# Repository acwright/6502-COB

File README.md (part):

6502-COB
========

An **AC6502** retro-style 8-bit computer based on the **65C02** microprocessor.

> 📖 **Guide:** [AC6502 Documentation](https://acwright.github.io/6502-DOCS/) — the user's and programmer's guide for the whole family.
> See [COB's page in the family appendix](https://acwright.github.io/6502-DOCS/family/cob).

---

**Building one? Every part you need, with supplier numbers and known issues, is in [BOM.md](BOM.md).**

## Table of Contents

- [Overview](#overview)
- [Architecture](#architecture)
- [Systems](#systems)
- [Software](#software)
- [Hardware](#hardware)
  - [Backplanes](#backplanes)
  - [Cards](#cards)
  - [Helpers](#helpers)
- [Which revision to make](#which-revision-to-make)
- [Firmware](#firmware)
  - [KEH Controller](#keh-controller)
  - [PS2 Keyboard Controller](#ps2-keyboard-controller)
  - [STP Controller](#stp-controller)
- [CAD](#cad)
- [Production](#production)
- [Schematics](#schematics)
- [Shared lines](#shared-lines)
- [Extra pins: `EXP0`–`EXP3` and `HRDB`](#extra-pins-exp0exp3-and-hrdb)
- [Jumpers](#jumpers)
- [Off-board headers](#off-board-headers)
- [Checking the schematics](#checking-the-schematics)
- [Libraries](#libraries)
- [Bill of Materials](#bill-of-materials)
- [Purchase](#purchase)
- [License](#license)

---

## Overview

The AC6502 ecosystem is a family of open-source, 65C02-based computers sharing a common architecture, memory map, and [BIOS](https://github.com/acwright/6502-BIOS). Each computer in the family is purpose-built for a different use case but runs the same software and firmware.

The **COB** (Computer on a Backplane) is a full-featured modular desktop computer. It features a real 65C02 CPU, a backplane architecture with expandable card slots, up to 544KB RAM, composite or VGA video output, CompactFlash or SD storage, a real-time clock, and support for PS/2 keyboards, matrix keyboards, and Atari 2600-compatible joysticks.

## Architecture

All AC6502 computers share:

- **CPU**: 65C02 (or accurate emulation)
- **Memory**: 32KB RAM + 32KB ROM, with optional banked RAM expansion
- **Memory Map**: Standardized across the ecosystem — zero page, stack, I/O space ($8000–$9FFF), system ROM, and interrupt vectors at $FFFA–$FFFF
- **Bus**: 16-bit address bus, 8-bit bidirectional data bus, standard 65C02 control signals (RW, PHI2, RESET, IRQ, NMI, RDY, SYNC)
- **BIOS**: A common [BIOS](https://github.com/acwright/6502-BIOS) provides the kernel, monitor, and BASIC interpreter across all systems

## Systems

| Project | Description |
|---------|-------------|
| [6502-ACE](https://github.com/acwright/6502-ACE) | All-in-one Computer Experience — A single board computer |
| [6502-COB](https://github.com/acwright/6502-COB) | Computer On a Backplane — Modular desktop computer with expandable card slots (YOU ARE HERE) |
| [6502-DEV](https://github.com/acwright/6502-DEV) | Development Environment Vehicle — Emulation-based dev system |
| [6502-KIM](https://github.com/acwright/6502-KIM) | Keypad Input Monitor - KIM-1 inspired minimal computer |
| [6502-VCS](https://github.com/acwright/6502-VCS) | Video Computer System — Cartridge-based retro gaming console |

## Software

| Project | Description |
|---------|-------------|
| [6502-BIOS](https://github.com/acwright/6502-BIOS) | The shared BIOS (kernel, monitor, BASIC) for all AC6502 computers |
| [6502-EMULATOR](https://github.com/acwright/6502-EMULATOR) | Emulator for the whole family — desktop app, browser build, and a command line for scripted runs |
| [6502-PRG](https://github.com/acwright/6502-PRG) | Template project for writing assembly language programs |
| [6502-CRT](https://github.com/acwright/6502-CRT) | Template project for writing assembly language cartridges |
| [6502-ASM](https://github.com/acwright/6502-ASM) | Assembly language example programs and demos |
| [6502-BAS](https://github.com/acwright/6502-BAS) | BASIC program listings |
| [6502-WOZMON](https://github.com/acwright/6502-WOZMON) | Wozmon as a standalone ROM |
| [6502-NOP](https://github.com/acwright/6502-NOP) | An all-NOP ROM, for probing a board during bring-up |
| [6502-DOCS](https://github.com/acwright/6502-DOCS) | The documentation site — the guide, the printable reference cards, branding and label artwork |
| [cffs](https://github.com/acwright/cffs) | Builds CompactFlash disk images for the BIOS filesystem |
| [bastok](https://github.com/acwright/bastok) | Tokenizes BASIC listings into `.prg` images, and back |
| [bin2woz](https://github.com/acwright/bin2woz) | Converts a binary into a Wozmon serial upload |

## Hardware

This repository contains KiCad 7.0+ PCB designs for the backplanes, cards, and helpers that make up the COB system.

### Backplanes

**`Hardware/Backplane/`** — Passive backplane providing 5 card slots with full bus interconnect across all slots.

**`Hardware/Backplane Pro/`** — Enhanced backplane with integrated clock generation, reset circuitry, and power distribution plus 5 card slots. Rev 1.1 moves to entirely through-hole components and adds an onboard power switch and DC barrel jack input. Today's Rev 1.1 also removes the `RESB` pull-up and adds reverse-polarity protection on the barrel jack; the boards made as Rev 1.1, which are on sale, have neither change (see the build notes in BOM.md). Every revision's oscillator can is 1 MHz, and serial is tested at 1 MHz. A faster can is at the builder's risk, because the serial cards haven't been tested with one.

**`Hardware/Backplane Helper/`** — Adds additional card slots to expand the total backplane configuration up to 12 slots.

### Cards

**`Hardware/Clock Card/`** — The Backplane Pro's clock, reset and power on a card, so a COB can be built on the passive Backplane: a 1 MHz DIP-14 can oscillator to `PHI2` through a clock-enable header (so the Clock Helper's single-step and halt still work), the 555 power-on and push-button reset pulling `RESB` low through an NPN, and a 5 V barrel jack with reverse-polarity protection. Serial is tested at 1 MHz, so a faster oscillator can is at the builder's risk, as on the Backplane Pro. *(Ordered, not yet built)*

**`Hardware/CPU Card/`** — Hosts the 65C02 CPU in a card form factor for backplane-based COB systems. Its `EXP` header, J3, can jumper `EXP0` to VPB and `EXP1` to MLB. Leave those two positions open in a build that takes cartridges, because a cartridge grounds `EXP0` and `EXP1` (see [Extra pins](#extra-pins-exp0exp3-and-hrdb)).

**`Hardware/CPU Card Pro/`** — Hosts a 65816 16-bit CPU (backward-compatible with 65C02). *(Untested)* Its title block credits bahamutkotd, who contributed. Its `EXP` header, J3, can jumper `EXP0` to VPB and `EXP1` to MLB; as on the CPU Card, leave those positions open in a build that takes cartridges. J2, `BANK ADDR`, carries the 65816's bank byte (address bits A16–A23), which U4 latches while `PHI2` is low and holds through the rest of the cycle. It is how a 65816 on this card reaches past 64 KB, for a breadboard or a card of your own. Nothing in the family uses it yet, and it is unproven until the card is built. The RAM Card Rev 1.0's J4 has the same pinout; see its build notes before joining the two.

**`Hardware/Memory Card/`** — Provides 32KB SRAM and 32KB EEPROM with address decoding logic for COB systems using the CPU Card. J2 (or the solder jumpers JP1 and JP2) joins the bus's `EXP1` and `EXP0` to the ROM's `HRDB`: fit both in a COB that takes cartridges. See [Extra pins](#extra-pins-exp0exp3-and-hrdb).

**`Hardware/RAM Card/`** — 512KB banked RAM expansion organized as two 256KB banks with 256 × 1KB windows each. Rev 1.1 has the ACE Board's circuit, with a bank latch for each window; Rev 1.0 has one latch for both. Rev 1.0's J4, `BANK ADDR`, carries the bank latch's outputs: an untested experiment that nothing in the family uses, which the build notes in [BOM.md](BOM.md#ram-card) explain.

**`Hardware/RTC Card/`** — Real-time clock via Dallas DS1511Y with battery backup and 256 bytes of battery-backed SRAM.

**`Hardware/GPIO Card/`** — General-purpose I/O via 65C22 VIA supporting keyboards, joysticks, timers, and custom devices.

**`Hardware/Serial Card/`** — RS-232 serial communication via R6551AP ACIA and MAX232 level shifter.
Female DB-9 wired as **DCE**, so a straight-through cable reaches a PC. `DCD` and `DSR` are tied to
ground; `DTR` is not connected. The `CTS EN` jumper (J4) picks whether the ACIA's `CTS` comes from
ground or from the cable — **ground is the default**, which leaves the transmitter always free to
send. Serial is tested at 1 MHz, the speed of the oscillator can on the Backplane Pro and the Clock
Card. A faster can is at the builder's risk.

**`Hardware/Serial Card Pro/`** — Enhanced serial card with full modem control signals (DTR, DCD, DSR).
Male DB-9 wired as **DTE**, like a PC, so reaching a laptop needs a **null-modem** cable — unlike the
plain Serial Card. `CTS`, `DSR` and `DTR` always reach the cable; the `DCD EN` jumper picks ground or
the cable for `DCD` — **ground is the default**. Serial is tested at 1 MHz, the speed of the
oscillator can on the Backplane Pro and the Clock Card. A faster can is at the builder's risk.

**The handshake lines are not decoration.** On a real R6551, measured on a KIM in 2026: `CTS` high
stops the transmitter dead, and `DCD` high stops the receiver and the arriving byte is lost. A card
jumpered to take either from the cable, plugged into something that does not assert them, looks like
a dead board — no banner, no echo — until the line comes back. Ground is the default for exactly
that reason.

**`Hardware/VGA Card/`** — VGA 640×480 video output via Raspberry Pi Pico running [Pico9918](https://github.com/visrealm/pico9918) with TMS9918A-compatible graphics modes.

**`Hardware/VGA Card Pro/`** — Fully programmable VGA output using Pi Pico with custom firmware. *(Untested)*

**`Hardware/Video Card/`** — Composite video output via TMS9918A Video Display Processor with 16KB video RAM.

**`Hardware/Video Card Pro/`** — Enhanced composite video card. *(Never made)*

**`Hardware/Sound Card/`** — 3-voice SID audio output via ARMSID module with RCA line-level output.

**`Hardware/Storage Card/`** — CompactFlash storage interface supporting up to 128GB via IDE-compatible protocol.

**`Hardware/Storage Card Pro/`** — SD card (up to 32GB) and 16MB onboard SPI flash storage interface. *(Untested, experimental — the stock BIOS has no driver for it; see [STP Controller](#stp-controller))*

**`Hardware/LCD Card/`** — 16×2 character LCD display via 65C22 VIA in 4-bit or 8-bit mode.

**`Hardware/Blinkenlights Card/`** — Visual bus monitoring with LEDs showing address bus (16), data bus (8), and control signals (8) in real time.

**`Hardware/Prototype Card/`** — Blank prototyping area with integrated breadboard and full bus access headers.

### Helpers

**`Hardware/Keyboard Encoder Helper/`** — ATmega1284-based dual keyboard encoder supporting PS/2 keyboard and 8×8 matrix keyboard simultaneously via 65C22 VIA.

**`Hardware/PS2 Helper/`** — ATmega328p-based PS/2 keyboard bridge that drives an MT8808 analog crosspoint switch to emulate a matrix keyboard. Its output is a raw 8×8 matrix and feeds the matrix inputs of a Keyboard Encoder Helper, which is what talks to the 65C22 VIA — not the VIA directly.

**`Hardware/Keyboard Helper/`** — 64-key matrix keyboard with Atari 2600-compatible joystick support.

**`Hardware/GPIO Helper/`** — 8 buttons and 8 LEDs for testing and debugging GPIO Card connections.

**`Hardware/GPIO Breadboard Helper/`** — Breadboard interface adapter for the GPIO Card.

**`Hardware/Joystick Helper/`** — Atari 2600-style dual joystick connector and interface board.

**`Hardware/Clock Helper/`** — Manual clock control providing single-step, free-run, and halt modes for debugging real CPU systems.

**`Hardware/DB25 Helper/`** — GPIO to DB25 connector adapter for external device interfacing.

**`Hardware/Breadboard Helper/`** — Exposes the full AC6502 bus to a breadboard for prototyping and experimentation.

**`Hardware/Mega Helper/`** — Arduino Mega 2560 interface adapter for the AC6502 bus. Arduino pins D6 and D5 are wired to `EXP1` and `EXP0`: with a cartridge on the bus, firmware must leave them as inputs, because the cartridge grounds them (see [Extra pins](#extra-pins-exp0exp3-and-hrdb)).

**LCD Board** — moved to [6502-DEV](https://github.com/acwright/6502-DEV) as the DEV LCD Board on 2026-11-14: it is a DEV board.

**`Hardware/VERA Helper/`** — VERA FPGA video module adapter for the AC6502 bus.

<!-- Which revision to make: generated by Tools/revision-audit/register.py from Tools/data/orders.json. Edit that file, not this section. -->
## Which revision to make

**Make the newest revision of a board, and check its label first.** The table below gives each board's newest revision. A newer revision fixes what was found on the older ones. Every revision, old and new, is in [REVISIONS.md](REVISIONS.md), with what changed in each.

Each revision carries one of three labels:

- **Tested:** This revision was built and tested.
- **Proven design:** Not built at this revision, but its circuit is a tested revision's. The only changes are silkscreen text, part values, mounting holes, outline clean-up, parts moved a fraction of a millimetre onto their grid, capacitor pitch, socket outlines, a footprint swap with the same holes, a solder jumper's default, the solder mask or paste at a card edge, or tracks rerouted or pours refilled with DRC and the netlist check passing. A builder can treat it as tested.
- **Untested:** The circuit, the power path or the layout changed in a way that only a built board proves, or the board has never been built at all.

[BOM.md](BOM.md) has the parts for every revision, and its known issues.

| Board | Newest revision | Label | Why |
|---|---|---|---|
| Backplane | 1.1 | **Proven design** | JLCPCB's marker removed and the logo moved; silkscreen only. |
| Backplane Helper | 1.1 | **Proven design** | JLCPCB's marker removed and the logo moved; silkscreen only. |
| Backplane Pro | 1.1 | **Untested** | The made Rev 1.1 with a 1N5819 in the power path (`VCC` near 4.6 V) and R5 removed. |
| Blinkenlights Card | 1.1 | **Untested** | Decoupling capacitors added, the RESB, IRQB and NMIB LEDs driven through inverters, every inverter a 74HC3G04, tracks rerouted, and the bare card edge. |
| Breadboard Helper | 1.1 | **Proven design** | J1 takes the box header's footprint, with the same holes, and the outline grows to hold it. |
| CPU Card | 1.1 | **Proven design** | 10k pull-ups, some tracks rerouted, silkscreen, the bare card edge. |
| CPU Card Pro | 1.1 | **Untested** | Never made. |
| Clock Card | 1.1 | **Untested** | The bare card edge only, but Rev 1.0 hasn't been tested yet. |
| Clock Helper | 1.1 | **Proven design** | Mounting holes moved to the standard, silkscreen. |
| DB25 Helper | 1.1 | **Proven design** | Mounting holes moved to the standard, silkscreen. |
| GPIO Breadboard Helper | 1.1 | **Proven design** | Outline clean-up. |
| GPIO Card | 1.1 | **Proven design** | The bare card edge only. |
| GPIO Helper | 1.1 | **Proven design** | Mounting holes moved to the standard, silkscreen. |
| Joystick Helper | 1.1 | **Proven design** | Mounting holes moved to the standard, silkscreen. |
| Keyboard Encoder Helper | 1.1 | **Proven design** | Mounting holes, silkscreen. |
| Keyboard Helper | 1.1 | **Proven design** | JLCPCB's marker removed and the logo moved; silkscreen only. |
| LCD Card | 1.1 | **Proven design** | The bare card edge only. |
| Mega Helper | 1.1 | **Proven design** | JLCPCB's marker removed, J1's reference resized and the logo moved; silkscreen only. |
| Memory Card | 1.1 | **Proven design** | The bare card edge, and a 74HCT00 at U5. |
| PS2 Helper | 1.1 | **Proven design** | Resistors moved and tracks rerouted, mounting holes, silkscreen. |
| Prototype Card | 1.1 | **Proven design** | The bare card edge only. |
| RAM Card | 1.1 | **Untested** | The ACE 1.1's banked-RAM circuit: a bank latch for each window, a diode chip select, a 74HCT00 for `RB` and `WB`, and no `LATCH EN` or `BANK ADDR` header. |
| RTC Card | 1.1 | **Proven design** | The bare card edge, and JP2 and JP3 removed, wired as Rev 1.0 ships them. |
| Serial Card | 1.1 | **Proven design** | Silkscreen text and the bare card edge. |
| Serial Card Pro | 1.1 | **Proven design** | The DB-9 moved to KiCad's standard footprint (the same connector), tracks rerouted, silkscreen, the bare card edge. |
| Sound Card | 1.1 | **Proven design** | Silkscreen text and the bare card edge. |
| Storage Card | 1.1 | **Proven design** | The bare card edge only. |
| Storage Card Pro | 1.1 | **Untested** | Silkscreen text and the bare card edge, but Rev 1.0 hasn't been tested. |
| VERA Helper | 1.1 | **Proven design** | Mounting holes, capacitor pitch, JP2 ships open, JP1 and JP3 removed and wired as Rev 1.0 ships them. |
| VGA Card | 1.1 | **Untested** | The pico9918 turned around, a new outline and jack mount, A1 wired to `MODE1`, the bare card edge, and JP2 and JP3 removed. |
| VGA Card Pro | 1.1 | **Untested** | Never made. |
| Video Card | 1.1 | **Proven design** | JP7, a solder jumper, ships bridged (fine with a real TMS9918A's open-drain `/INT`), JP1–JP6 removed and wired as Rev 1.0 ships them, sockets, silkscreen, the bare card edge. |
| Video Card Pro | 1.1 | **Untested** | Never made. |
<!-- End of which revision to make -->

## Firmware

This repository contains [PlatformIO](https://platformio.org/)-based firmware for the COB system's microcontroller helpers.

### KEH Controller
`Firmware/KEH Controller/`

Firmware for the ATmega1284 on the Keyboard Encoder Helper. Provides:

- Simultaneous PS/2 keyboard and 8×8 matrix keyboard scanning
- ASCII conversion with modifier key support (Shift, Ctrl)
- Buffered, debounced input handling
- Parallel I/O to the AC6502 bus via 65C22 VIA

See [Firmware/KEH Controller/README.md](./Firmware/KEH%20Controller/README.md) for setup and usage instructions.

### PS2 Keyboard Controller
`Firmware/PS2 Keyboard Controller/`

Firmware for the ATmega328p on the PS2 Helper. Provides:

- Interrupt-driven PS/2 keyboard scan code reading
- MT8808 analog crosspoint switch matrix control
- Make/break detection and extended scan code support
- Function key emulation via FN key combinations

The MT8808 closes row/column contacts in place of physical key switches, so this
card connects to the **matrix inputs of a Keyboard Encoder Helper**, not to a
65C22 VIA. The encoder does the scanning and ASCII conversion; wired straight to
a VIA the card produces nothing, as the BIOS has no matrix-scanning code.

See [Firmware/PS2 Keyboard Controller/README.md](./Firmware/PS2%20Keyboard%20Controller/README.md) for setup and usage instructions.

### STP Controller
`Firmware/STP Controller/`

Firmware for the ATmega328p on the Storage Card Pro. Provides:

- Memory-mapped SPI controller for 6502 bus access
- Support for SD card, 16MB SPI flash, and external SPI devices
- Dual-speed SPI (4 MHz normal operation, 400 kHz initialization)
- PHI2-synchronized interface for reliable 6502 communication

⚠️ **Experimental.** The Storage Card Pro is not part of the default I/O set the
BIOS probes for, and no COB machine is built around it today. The BIOS storage
slot expects eight True IDE CompactFlash registers at `$8C00–$8C07`; this card
presents two SPI registers instead, so a stock BIOS reports `NO DEVICE` for every
storage path. Using it needs a modified BIOS or software that drives the two
registers directly.

See [Firmware/STP Controller/README.md](./Firmware/STP%20Controller/README.md) for setup and usage instructions.

## CAD
`CAD/`

3D-printable enclosure parts and laser-cut top panels for the COB system.

**Board images** are in `CAD/Images/<Board>/Rev X/`: `Front.png` and `Back.png` on white, and `Front Transparent.png` and `Back Transparent.png` with no background. Every image is a 3D render at the same size, with the black solder mask and white silkscreen the boards are made with. Bare-board photos may differ, because the renders show parts fitted.

**Top panels, enclosures and jigs are versioned by board revision**, like `Hardware/`: `CAD/Tops/<Board>/Rev X/`, `CAD/Enclosures/<Board>/Rev X/`, `CAD/Jigs/<Board>/Rev X/`. Each revision has its own complete folder, even when two revisions share the same files. `Bases/` holds the parts for a whole computer, not for one board, so it isn't versioned.

Keyboard Encoder Helper Rev 1.0, the board on sale, has the old 88 × 39 mm holes, and the COB's base plate is drilled for Rev 1.1's 88 × 38 mm. To fit a Rev 1.0 board, drill plate holes 9 and 21 (x 296, at y 16 and y 104 on the plate mounting drawing) out to 5 mm. The two screws then sit 1 mm to the left of those holes' centers, and the board moves less than 1 mm into the 10 mm gap beside the Backplane Helper. Drill through all three layers of the plate, and add a washer if a screw head doesn't sit flat. The plate mounting drawing itself shows Rev 1.1.

The Rev 1.0 top panels for the Clock, DB25, GPIO, Joystick and Keyboard Encoder Helpers, and the Rev 1.1 top panel for the PS2 Helper, are derived from the other revision's panel by moving the four mounting holes. None of them has been cut yet.

The **[plate mounting drawing](CAD/Bases/Plate%20Mounting%20Drawing.png)** ([SVG](CAD/Bases/Plate%20Mounting%20Drawing.svg)) shows where the two Backplanes (each a Backplane or a Backplane Pro), the Backplane Helper and the Keyboard Encoder Helper mount on the base plate, with every hole's position and the hardware the build needs. The plate is a stack of three 3 mm acrylic layers.

## Production
`Production/`

[REVISIONS.md](REVISIONS.md) lists every board revision: whether it was made, its JLCPCB order, the commit it was made from, and what fits it.

JLCPCB-ready Gerber files and BOM/CPL for PCB fabrication and assembly.

## Schematics
`Schematics/`

PDF schematics for each board.

## Shared lines

Five lines of the 6502 bus are shared by every board on it: `RESB`, `IRQB`, `NMIB`, `RDY` and `BE`. A board may pull one of these lines low, and nothing drives one high. Each line is held high by one 10kΩ pull-up resistor to VCC, on the board with the CPU: the ACE Board, the KIM Board, the VCS Main Board, the COB CPU Card or CPU Card Pro, or the DEV Board. No other board has one. Two pull-ups on the same line would sit in parallel and lower its resistance, so a card that adds its own pull-up changes the machine for every other board. The VIAs and PIAs in the BOMs, the W65C22N and W65C21N, have open-drain interrupt outputs for this reason.

**Interrupt outputs.** Whatever drives `IRQB` or `NMIB` may only pull it low. Every board is drawn for the parts in its BOM and works as shipped, with no jumper to cut or bridge:

- **A part whose interrupt output is open-drain** (the W65C22N, W65C21N, R6551AP, DS1511Y and TMS9918A) drives the line directly, or through a diode with a solder jumper across it that ships bridged. The diode is fitted either way. To use a part that drives its interrupt high as well as low instead, such as a W65C22S or a replacement of your own, cut the jumper: the diode then lets the part only pull the line low. A board with no diode in the line can't take such a part.
- **A part that drives its interrupt high as well as low** (the pico9918, the VERA module, and a microcontroller such as the ATmega1284 or a Raspberry Pi Pico) reaches the line through a diode, a BAT85 or a 1N914, with its cathode toward the part. Where a solder jumper sits across that diode, it ships open. The diode is then the only path to the line, so fit it, and never bridge the jumper, because the part would then hold the line high against every other interrupt source.
- **A microcontroller wired to the line directly,** as on the ACE Board, the Mega Helper and the Flash Helper, drives it open-drain in its firmware: it sets the pin low or leaves it as an input, and never drives it high.

The *Jumpers* section below gives each board's interrupt jumper.

The same holds where a board has its own reset circuit. A reset switch, its timer and the transistor that pulls `RESB` low can be on any board, such as the COB Backplane Pro or the Clock Card, but the `RESB` pull-up is only ever on the board with the CPU. Each of those boards draws its pull-ups together, in one group on its schematic.

The DEV Board is the exception on `RESB`. It stands in for a Main Board, so it owns reset: its Reset button goes to the Teensy, and the Teensy drives `RESB` onto the bus through U3, a level shifter that only sends signals out, as it drives `PHI2`. U3 holds `RESB` high or low, so the DEV Board has no `RESB` pull-up, and nothing else on its bus may pull `RESB` low. Connect a DEV only to a passive backplane, never to the COB Backplane Pro, whose reset circuit would pull against U3, and don't fit a card that pulls `RESB` low, such as the COB RTC Card.

`SOB` is a CPU pin that isn't on the bus. It is tied to VCC, directly or through a 10kΩ resistor.

A few chips have a pull-up of their own inside the chip, such as an ATmega's reset pin. Where such a pin is wired to `RESB`, its pull-up of 30–60kΩ sits in parallel with the 10kΩ one. That's harmless, because whatever pulls `RESB` low can sink the extra current many times over.

A revision that doesn't follow this yet says so in its known issues in [BOM.md](BOM.md), with what to fit or remove.

## Extra pins: `EXP0`–`EXP3` and `HRDB`

`EXP` stands for "extra pin". Four pins of the 6502 bus are left for a builder's own use: pin 4 is `EXP1`, pin 6 is `EXP0`, pin 19 is `EXP3` and pin 21 is `EXP2`.

Pins 4 and 6 have a second job. A cartridge ties both of them to GND. That pulls `HRDB` ("High ROM disable bar", active low) low on the board with the ROM, which takes `$C000–$FFFF` away from the ROM so that the cartridge answers there instead. So in a build that uses cartridges, pins 4 and 6 are reserved for `HRDB`, and nothing else may drive them. They are free as `EXP1` and `EXP0` only in a build that never uses cartridges. `EXP2` and `EXP3` are always free.

How the boards treat pins 4 and 6:

- **The ACE Board and the KIM Board** join them to their ROM's `HRDB` input, and their silk says `HRDB`. The VCS Main Board joins them the same way from Rev 1.1.
- **The COB Memory Card** joins them to its `HRDB` only through jumpers: fit two shunts on J2, or bridge JP1 and JP2, in a COB that takes cartridges. It is the only board with these jumpers, because the COB is the experimenter's build. The VCS Main Board Rev 1.0 had them too (J5, or JP3 and JP4); fit them, because the VCS always takes cartridges.
- **A cartridge** (the ROM Cart, the Flash Cart, the KIM Keypad Card) ties them to GND.
- **A board that only carries the bus through**, such as a backplane or a helper, calls them `EXP1` and `EXP0`, as its silk does, and a note on its schematic says what they carry.

<!-- Jumpers: generated by Tools/jumpers/gen.py from Tools/data/jumpers.json. Edit that file, not this section. -->
## Jumpers

Some boards have solder jumpers, and pin headers that take a shunt. The tables below give every one: what it's for, how the board is shipped, and what to do with it. The **Needed** column marks the ones that matter:

- **To run**: the board doesn't work until this is set. Set it before the first power-up.
- **For serial**, **For interrupts**, **For cartridges**: the board runs without it, but that feature doesn't.
- Blank: leave it as shipped unless you want what it offers.

Where a header needs a shunt, the board's BOM lists it.

**Backplane Pro**

| Rev | Jumper | What it's for | As shipped | What to do | Needed |
|---|---|---|---|---|---|
| 1.0 | JP1, J1 | Power: JP1 is across J1 (`PWR_SW`), the header for a power switch on a case. | Open. | Bridge JP1, or wire a switch to J1. Until one is done the backplane has no power. | To run |
| 1.0 | JP2, J4 | Clock: JP2 is across J4 (`CLOCK_ENBL_SW`), the header for a switch that stops the clock. | Open. | Bridge JP2, or wire a switch to J4. Until one is done there is no clock on `PHI2`. | To run |
| 1.1 | JP1, J5 | Clock: JP1 is across J5 (`CLOCK ENBL SW`), the header for a switch that stops the clock. | Open. | Bridge JP1, or wire a switch to J5. Until one is done there is no clock on `PHI2`. | To run |

**CPU Card**

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
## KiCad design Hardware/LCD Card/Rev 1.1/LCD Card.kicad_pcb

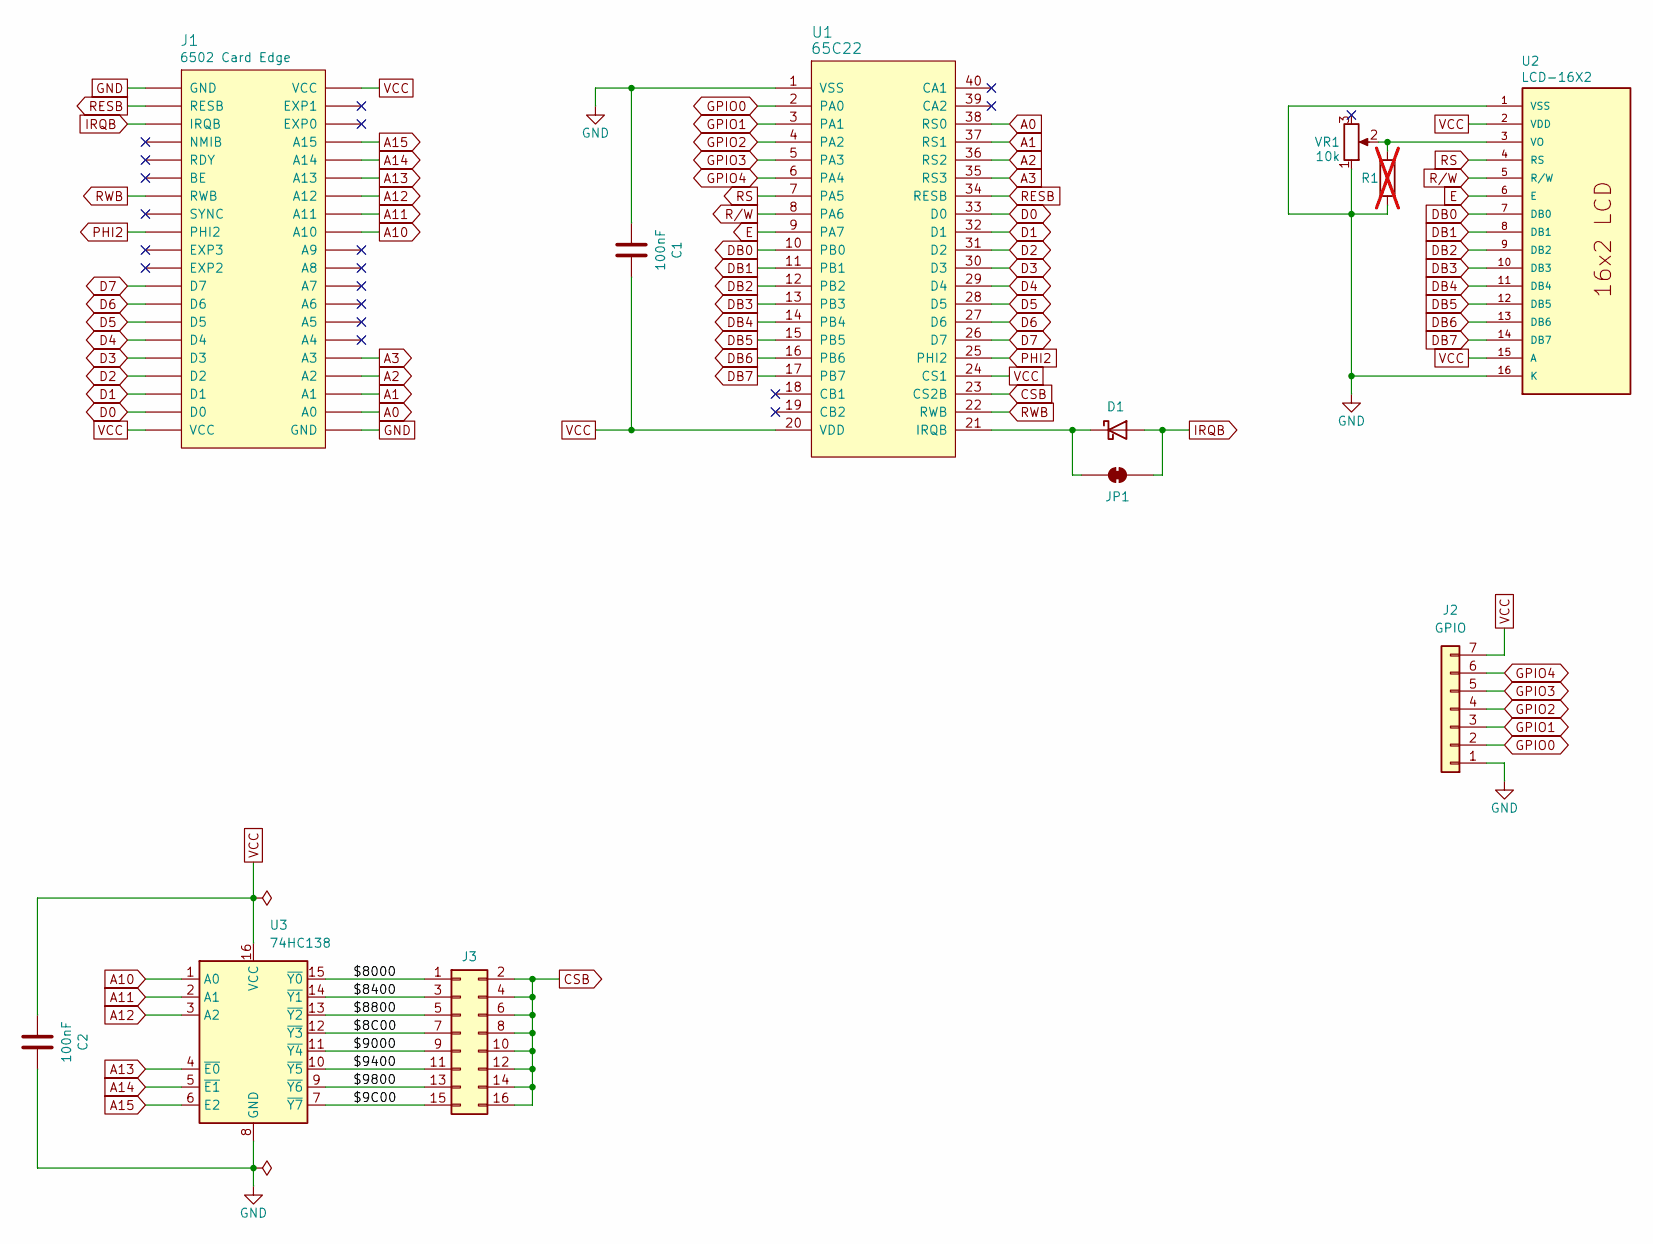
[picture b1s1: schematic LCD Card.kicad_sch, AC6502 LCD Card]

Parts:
C1, C2: 100nF; C_0805_2012Metric; LCSC C49678
D1: BAT85; D_DO-35_SOD27_P7.62mm_Horizontal; Digikey BAT85SCT-ND
J1: 6502 Card Edge
J2: GPIO; PinHeader_1x07_P2.54mm_Horizontal; Digikey 2057-PH1RB-07-UA-ND
J3: Conn_02x08_Odd_Even; PinHeader_2x08_P2.54mm_Vertical; Digikey S2011EC-40-ND
JP1: SolderJumper_2_Bridged; SolderJumper-2_P1.3mm_Bridged_RoundedPad1.0x1.5mm
R1: DNP: parallel with VR1 to make ~10 k; R_Axial_DIN0204_L3.6mm_D1.6mm_P5.08mm_Horizontal; not fitted
U1: 65C22; DIP-40_W15.24mm_Socket_LongPads; Mouser 955-W65C22N6TPG-14
U2: LCD-16X2
U3: 74HC138; SOIC-16_3.9x9.9mm_P1.27mm; LCSC C5602
VR1: 10k; Trimmer 3386F; Digikey 3386F-103LF-ND

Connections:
/$8C00: J3.7, U3.12 (~Y3)
/$9C00: J3.15, U3.7 (~Y7)
/$8000: J3.1, U3.15 (~Y0)
/$8400: J3.3, U3.14 (~Y1)
/$8800: J3.5, U3.13 (~Y2)
/$9000: J3.9, U3.11 (~Y4)
/$9400: J3.11, U3.10 (~Y5)
/$9800: J3.13, U3.9 (~Y6)
A0: J1.A0, U1.38 (RS0)
A1: J1.A1, U1.37 (RS1)
A2: J1.A2, U1.36 (RS2)
A3: J1.A3, U1.35 (RS3)
A10: J1.A10, U3.1 (A0)
A11: J1.A11, U3.2 (A1)
A12: J1.A12, U3.3 (A2)
A13: J1.A13, U3.4 (~E0)
A14: J1.A14, U3.5 (~E1)
A15: J1.A15, U3.6 (E2)
CSB: J3.2, J3.4, J3.6, J3.8, J3.10, J3.12, J3.14, J3.16, U1.23 (CS2B)
D0: J1.D0, U1.33 (D0)
D1: J1.D1, U1.32 (D1)
D2: J1.D2, U1.31 (D2)
D3: J1.D3, U1.30 (D3)
D4: J1.D4, U1.29 (D4)
D5: J1.D5, U1.28 (D5)
D6: J1.D6, U1.27 (D6)
D7: J1.D7, U1.26 (D7)
DB0: U1.10 (PB0), U2.7 (DB0)
DB1: U1.11 (PB1), U2.8 (DB1)
DB2: U1.12 (PB2), U2.9 (DB2)
DB3: U1.13 (PB3), U2.10 (DB3)
DB4: U1.14 (PB4), U2.11 (DB4)
DB5: U1.15 (PB5), U2.12 (DB5)
DB6: U1.16 (PB6), U2.13 (DB6)
DB7: U1.17 (PB7), U2.14 (DB7)
E: U1.9 (PA7), U2.6 (E)
GND: C1.1, C2.2, J1.GND, J2.1, R1.2, U1.1 (VSS), U2.1 (VSS), U2.16 (K), U3.8 (GND), VR1.1
GPIO0: J2.2, U1.2 (PA0)
GPIO1: J2.3, U1.3 (PA1)
GPIO2: J2.4, U1.4 (PA2)
GPIO3: J2.5, U1.5 (PA3)
GPIO4: J2.6, U1.6 (PA4)
IRQB: D1.2 (A), J1.IRQB, JP1.2 (B)
unnamed: D1.1 (K), JP1.1 (A), U1.21 (IRQB)
unnamed: R1.1, U2.3 (VO), VR1.2
PHI2: J1.PHI2, U1.25 (PHI2)
RESB: J1.RESB, U1.34 (RESB)
RS: U1.7 (PA5), U2.4 (RS)
RWB: J1.RWB, U1.22 (RWB)
R/W: U1.8 (PA6), U2.5 (R/W)
VCC: C1.2, C2.1, J1.VCC, J2.7, U1.20 (VDD), U1.24 (CS1), U2.2 (VDD), U2.15 (A), U3.16 (VCC)

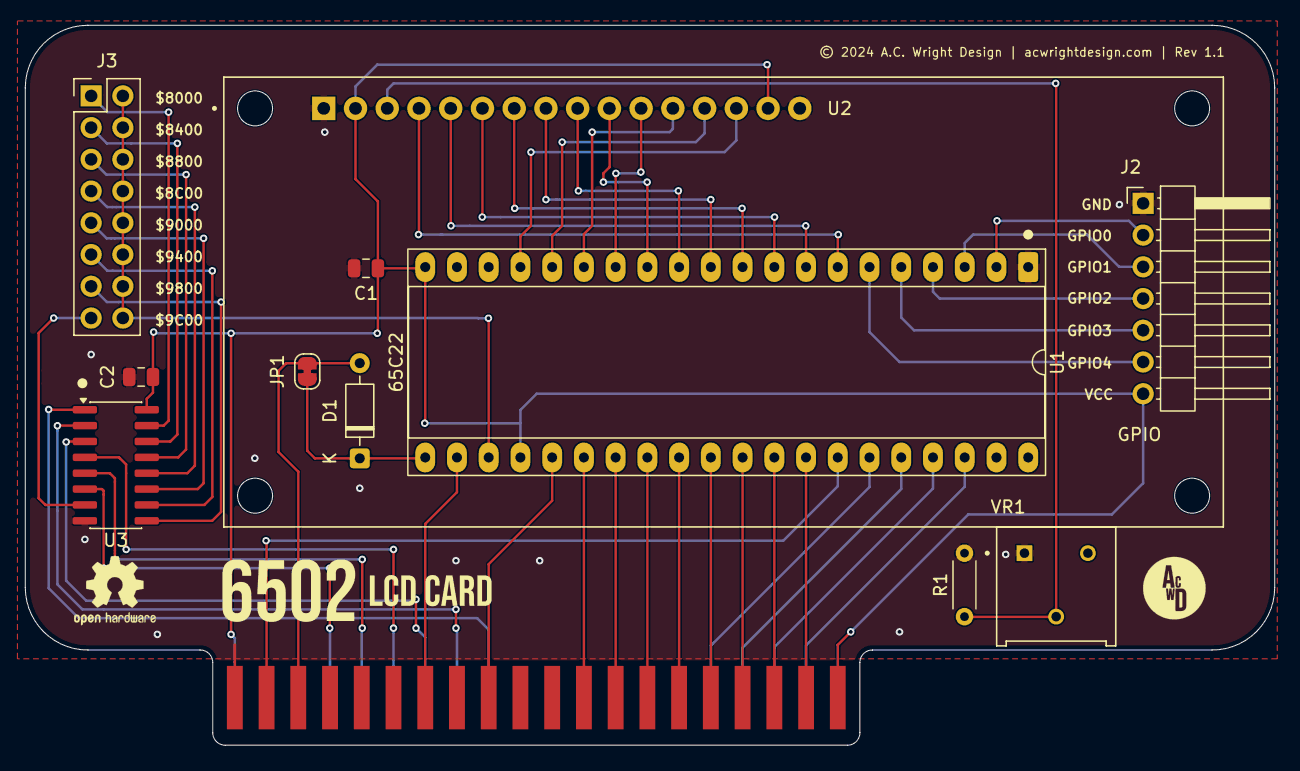
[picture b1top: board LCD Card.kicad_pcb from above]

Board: 2 copper layers, 100.0 x 57.6 mm, 12 parts (0 on the bottom side), 51 nets.

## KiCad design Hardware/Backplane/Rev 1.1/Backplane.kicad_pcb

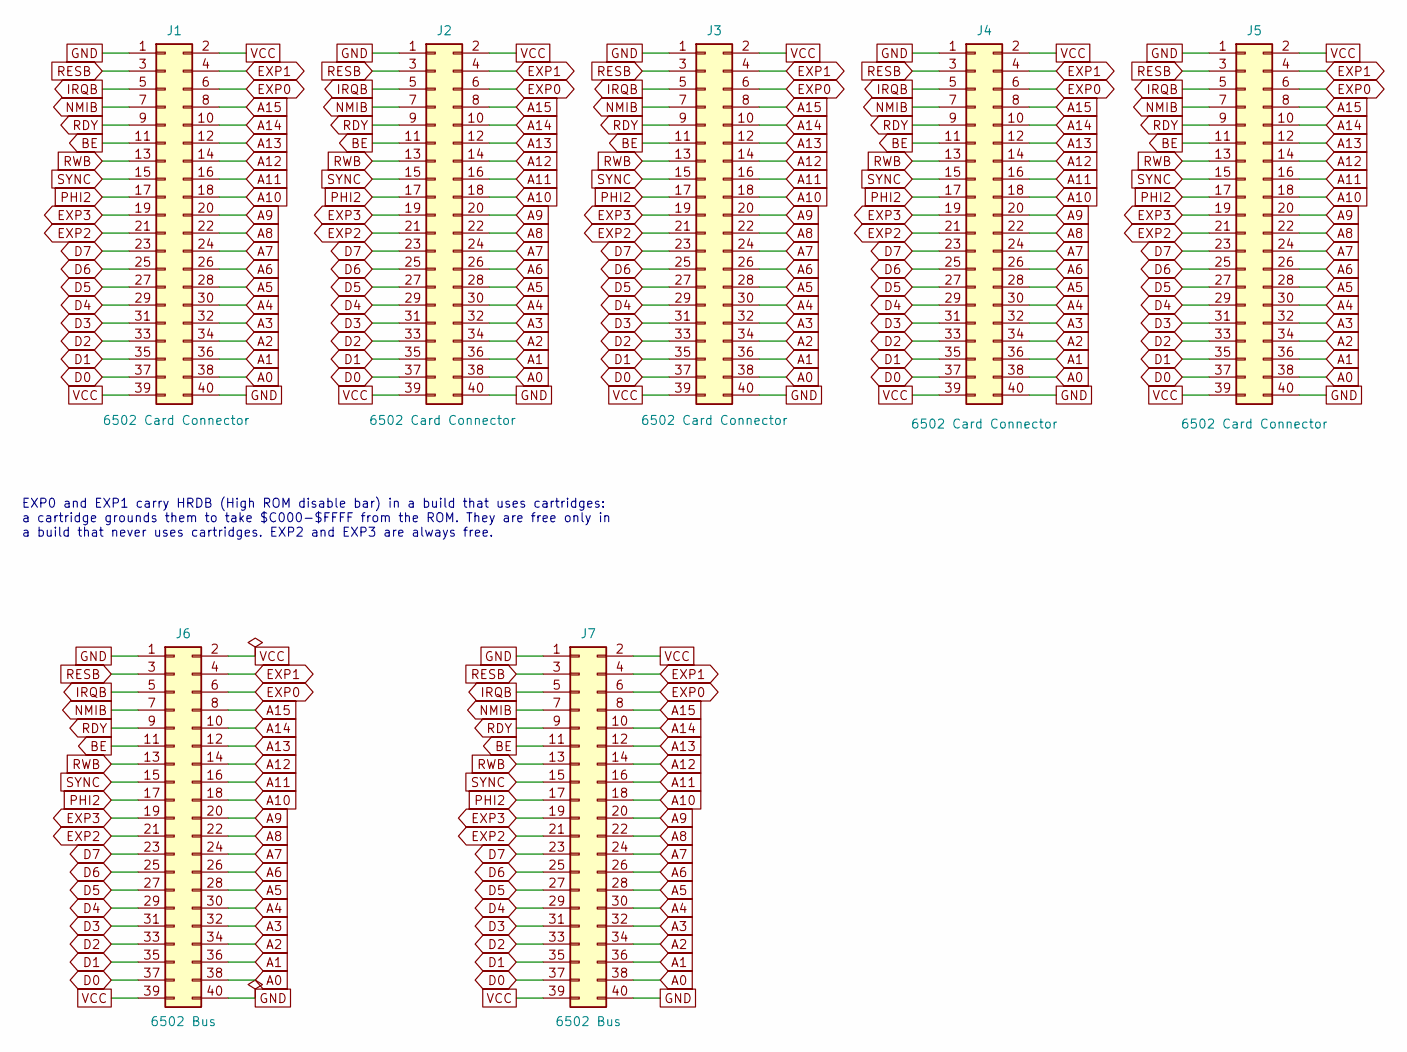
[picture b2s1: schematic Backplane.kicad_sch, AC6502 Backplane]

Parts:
J1, J2, J3, J4, J5: 6502 Card Connector; 6502 Card Slot; Mouser 571-5-5530843-4
J6, J7: 6502 Bus; 6502 Bus Connector; Digikey 732-5401-ND

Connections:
A0: J1.38, J2.38, J3.38, J4.38, J5.38, J6.38, J7.38
A1: J1.36, J2.36, J3.36, J4.36, J5.36, J6.36, J7.36
A2: J1.34, J2.34, J3.34, J4.34, J5.34, J6.34, J7.34
A3: J1.32, J2.32, J3.32, J4.32, J5.32, J6.32, J7.32
A4: J1.30, J2.30, J3.30, J4.30, J5.30, J6.30, J7.30
A5: J1.28, J2.28, J3.28, J4.28, J5.28, J6.28, J7.28
A6: J1.26, J2.26, J3.26, J4.26, J5.26, J6.26, J7.26
A7: J1.24, J2.24, J3.24, J4.24, J5.24, J6.24, J7.24
A8: J1.22, J2.22, J3.22, J4.22, J5.22, J6.22, J7.22
A9: J1.20, J2.20, J3.20, J4.20, J5.20, J6.20, J7.20
A10: J1.18, J2.18, J3.18, J4.18, J5.18, J6.18, J7.18
A11: J1.16, J2.16, J3.16, J4.16, J5.16, J6.16, J7.16
A12: J1.14, J2.14, J3.14, J4.14, J5.14, J6.14, J7.14
A13: J1.12, J2.12, J3.12, J4.12, J5.12, J6.12, J7.12
A14: J1.10, J2.10, J3.10, J4.10, J5.10, J6.10, J7.10
A15: J1.8, J2.8, J3.8, J4.8, J5.8, J6.8, J7.8
BE: J1.11, J2.11, J3.11, J4.11, J5.11, J6.11, J7.11
D0: J1.37, J2.37, J3.37, J4.37, J5.37, J6.37, J7.37
D1: J1.35, J2.35, J3.35, J4.35, J5.35, J6.35, J7.35
D2: J1.33, J2.33, J3.33, J4.33, J5.33, J6.33, J7.33
D3: J1.31, J2.31, J3.31, J4.31, J5.31, J6.31, J7.31
D4: J1.29, J2.29, J3.29, J4.29, J5.29, J6.29, J7.29
D5: J1.27, J2.27, J3.27, J4.27, J5.27, J6.27, J7.27
D6: J1.25, J2.25, J3.25, J4.25, J5.25, J6.25, J7.25
D7: J1.23, J2.23, J3.23, J4.23, J5.23, J6.23, J7.23
EXP0: J1.6, J2.6, J3.6, J4.6, J5.6, J6.6, J7.6
EXP1: J1.4, J2.4, J3.4, J4.4, J5.4, J6.4, J7.4
EXP2: J1.21, J2.21, J3.21, J4.21, J5.21, J6.21, J7.21
EXP3: J1.19, J2.19, J3.19, J4.19, J5.19, J6.19, J7.19
GND: J1.1, J1.40, J2.1, J2.40, J3.1, J3.40, J4.1, J4.40, J5.1, J5.40, J6.1, J6.40, J7.1, J7.40
IRQB: J1.5, J2.5, J3.5, J4.5, J5.5, J6.5, J7.5
NMIB: J1.7, J2.7, J3.7, J4.7, J5.7, J6.7, J7.7
PHI2: J1.17, J2.17, J3.17, J4.17, J5.17, J6.17, J7.17
RDY: J1.9, J2.9, J3.9, J4.9, J5.9, J6.9, J7.9
RESB: J1.3, J2.3, J3.3, J4.3, J5.3, J6.3, J7.3
RWB: J1.13, J2.13, J3.13, J4.13, J5.13, J6.13, J7.13
SYNC: J1.15, J2.15, J3.15, J4.15, J5.15, J6.15, J7.15
VCC: J1.2, J1.39, J2.2, J2.39, J3.2, J3.39, J4.2, J4.39, J5.2, J5.39, J6.2, J6.39, J7.2, J7.39

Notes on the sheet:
EXP0 and EXP1 carry HRDB (High ROM disable bar) in a build that uses cartridges: a cartridge grounds them to take $C000-$FFFF from the ROM. They are free only in a build that never uses cartridges. EXP2 and EXP3 are always free.

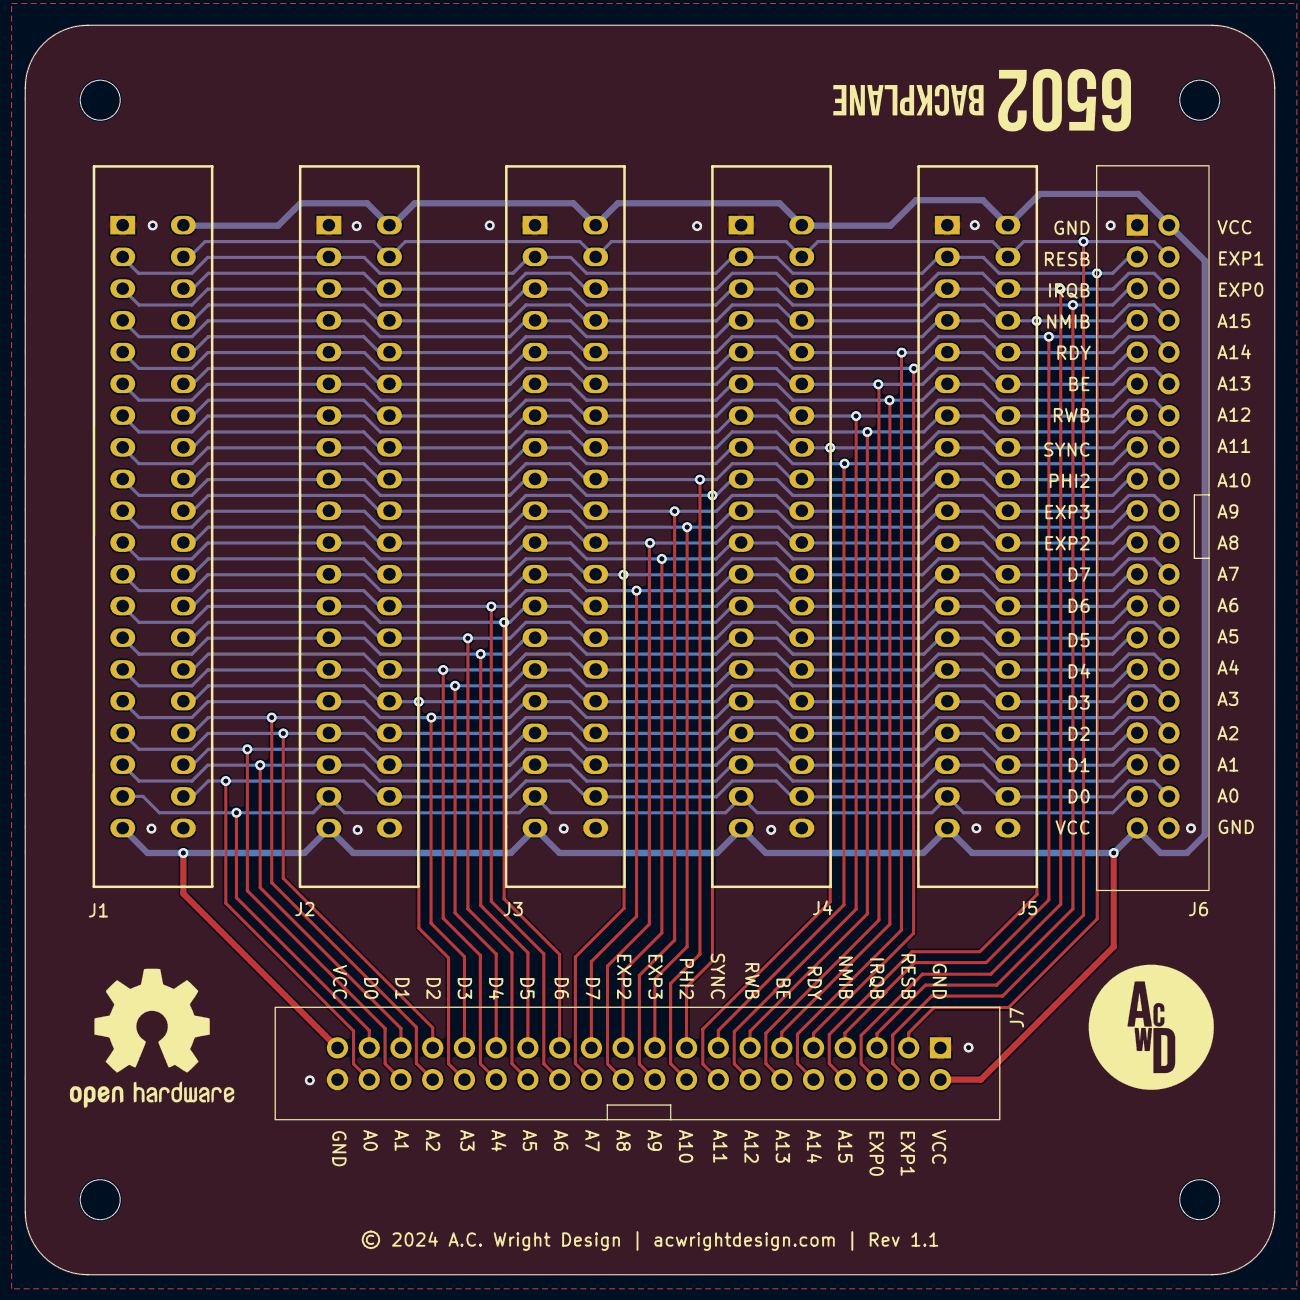
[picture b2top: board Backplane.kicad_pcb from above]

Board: 2 copper layers, 100.0 x 100.0 mm, 11 parts (0 on the bottom side), 38 nets.

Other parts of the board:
H1, H2, H3, H4: MountingHole; MountingHole_3.2mm_M3

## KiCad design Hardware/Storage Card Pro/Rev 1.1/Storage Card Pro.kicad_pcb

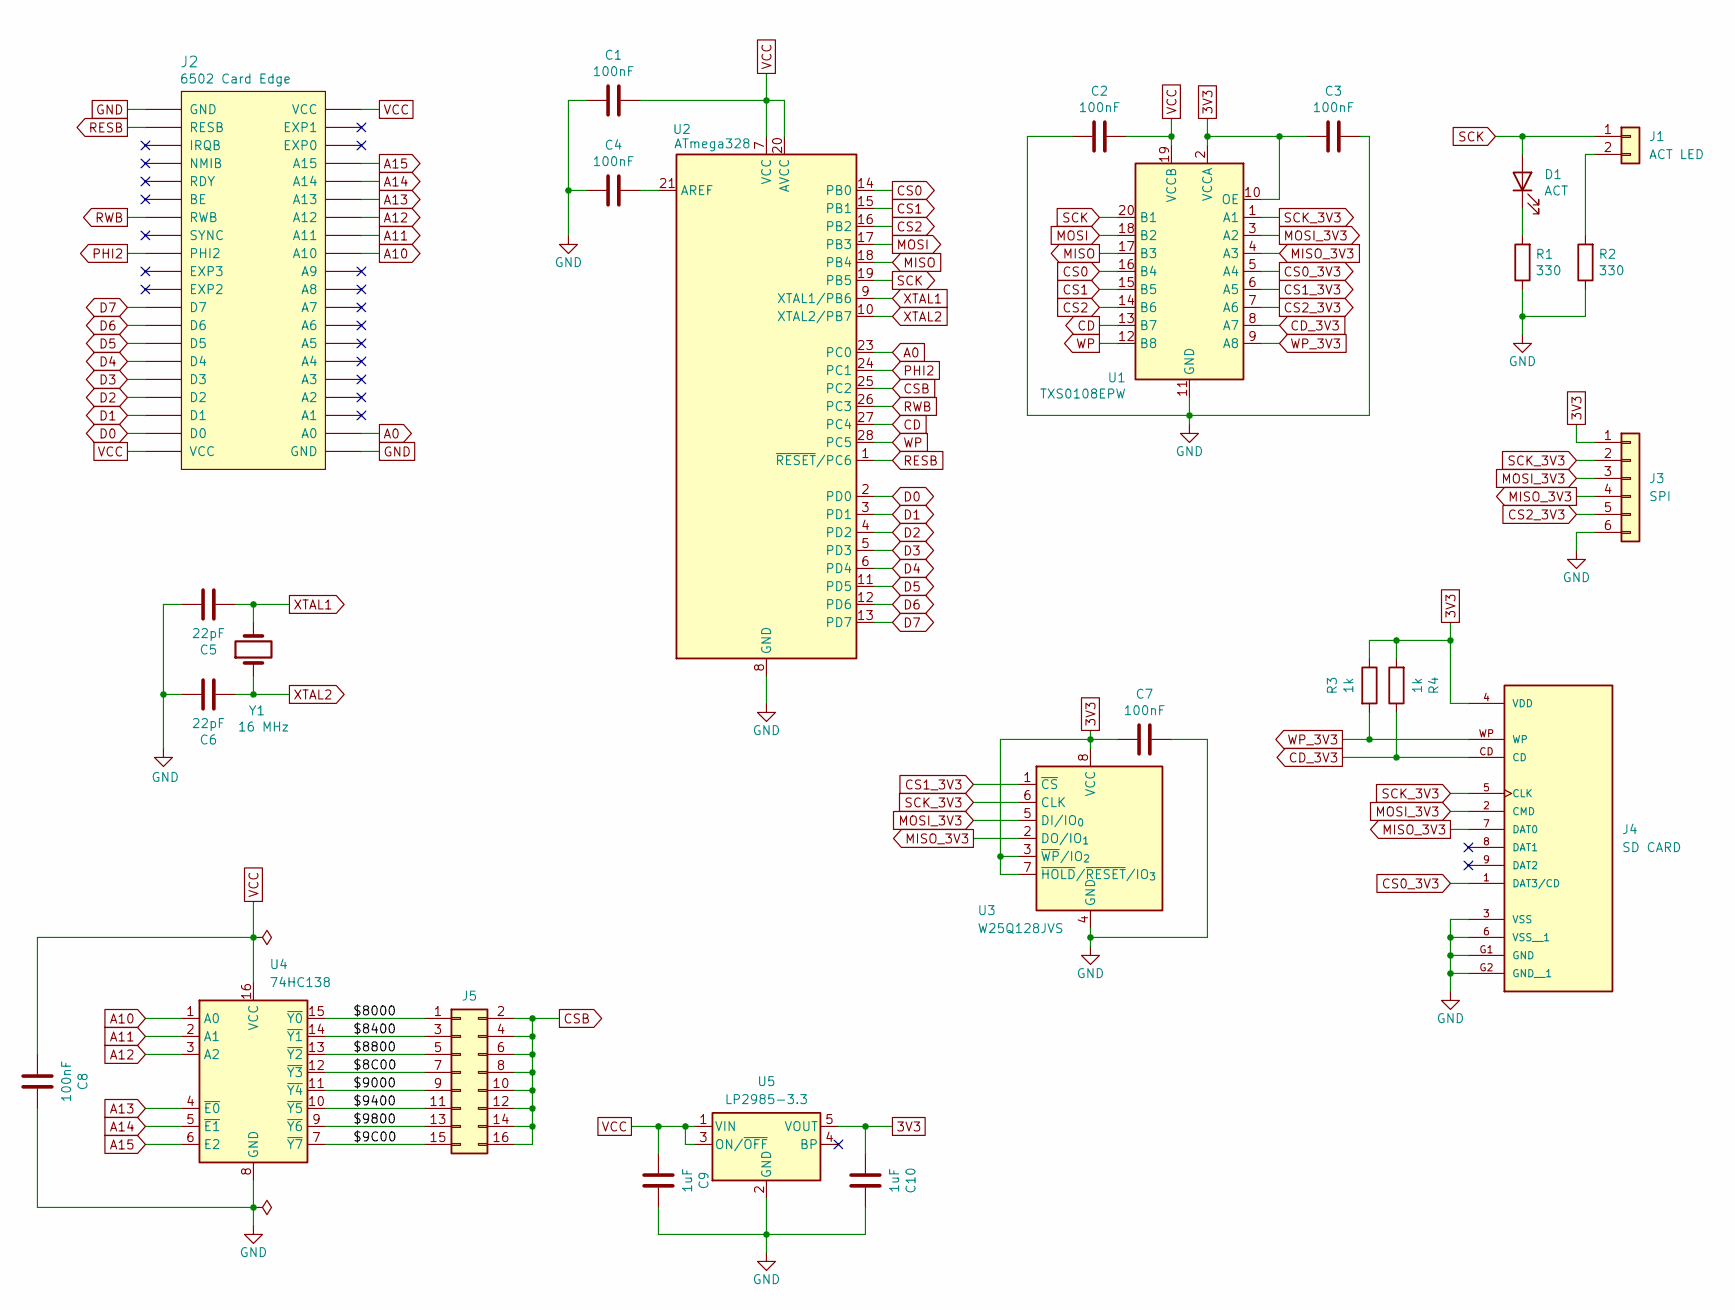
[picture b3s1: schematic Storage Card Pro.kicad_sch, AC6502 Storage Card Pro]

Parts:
C1, C2, C3, C4, C7, C8: 100nF; C_0805_2012Metric; LCSC C49678
C5, C6: 22pF; C_Disc_D5.0mm_W2.5mm_P2.50mm; Digikey 478-4846-ND
C9, C10: 1uF; C_0805_2012Metric; LCSC C28323
D1: ACT; LED_0805_2012Metric; LCSC C2297
J1: ACT LED; JST_XH_B2B-XH-A_1x02_P2.50mm_Vertical; Digikey 455-B2B-XH-A-ND
J2: 6502 Card Edge
J3: SPI; PinHeader_1x06_P2.54mm_Horizontal; Digikey 2057-PH1RB-06-UA-ND
J4: SD CARD; microSD Socket; LCSC C569097
J5: Conn_02x08_Odd_Even; PinHeader_2x08_P2.54mm_Vertical; Digikey S2011EC-40-ND
R1, R2: 330; R_0805_2012Metric; LCSC C17630
R3, R4: 1k; R_0805_2012Metric; LCSC C17513
U1: TXS0108EPW; TSSOP-20_4.4x6.5mm_P0.65mm; LCSC C17206
U2: ATmega328; DIP-28_W7.62mm_Socket_LongPads; Digikey ATMEGA328P-PU-ND
U3: W25Q128JVS; SOIC-8_5.3x5.3mm_P1.27mm; LCSC C97521
U4: 74HC138; SOIC-16_3.9x9.9mm_P1.27mm; LCSC C5602
U5: LP2985-3.3; SOT-23-5; LCSC C95414
Y1: 16 MHz; Crystal_HC49-U_Vertical; Digikey X1103-ND

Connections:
3V3: C3.1, C7.1, C10.1, J3.1, J4.4 (VDD), R3.1, R4.2, U1.2 (VCCA), U1.10 (OE), U3.3 (~WP/IO_{2}), U3.7 (~HOLD/~RESET/IO_{3}), U3.8 (VCC), U5.5 (VOUT)
/$8C00: J5.7, U4.12 (~Y3)
/$9C00: J5.15, U4.7 (~Y7)
/$8000: J5.1, U4.15 (~Y0)
/$8400: J5.3, U4.14 (~Y1)
/$8800: J5.5, U4.13 (~Y2)
/$9000: J5.9, U4.11 (~Y4)
/$9400: J5.11, U4.10 (~Y5)
/$9800: J5.13, U4.9 (~Y6)
A0: J2.A0, U2.23 (PC0)
A10: J2.A10, U4.1 (A0)
A11: J2.A11, U4.2 (A1)
A12: J2.A12, U4.3 (A2)
A13: J2.A13, U4.4 (~E0)
A14: J2.A14, U4.5 (~E1)
A15: J2.A15, U4.6 (E2)
CD: U1.13 (B7), U2.27 (PC4)
CD_3V3: J4.CD, R4.1, U1.8 (A7)
CS0: U1.16 (B4), U2.14 (PB0)
CS0_3V3: J4.1 (DAT3/CD), U1.5 (A4)
CS1: U1.15 (B5), U2.15 (PB1)
CS1_3V3: U1.6 (A5), U3.1 (~CS)
CS2: U1.14 (B6), U2.16 (PB2)
CS2_3V3: J3.5, U1.7 (A6)
CSB: J5.2, J5.4, J5.6, J5.8, J5.10, J5.12, J5.14, J5.16, U2.25 (PC2)
D0: J2.D0, U2.2 (PD0)
D1: J2.D1, U2.3 (PD1)
D2: J2.D2, U2.4 (PD2)
D3: J2.D3, U2.5 (PD3)
D4: J2.D4, U2.6 (PD4)
D5: J2.D5, U2.11 (PD5)
D6: J2.D6, U2.12 (PD6)
D7: J2.D7, U2.13 (PD7)
GND: C1.1, C2.1, C3.2, C4.1, C5.2, C6.2, C7.2, C8.2, C9.2, C10.2, J2.GND, J3.6, J4.3 (VSS), J4.6 (VSS__1), J4.G1 (GND), J4.G2 (GND__1), R1.1, R2.1, U1.11 (GND), U2.8 (GND), U2.22 (GND), U3.4 (GND), U4.8 (GND), U5.2 (GND)
MISO: U1.17 (B3), U2.18 (PB4)
MISO_3V3: J3.4, J4.7 (DAT0), U1.4 (A3), U3.2 (DO/IO_{1})
MOSI: U1.18 (B2), U2.17 (PB3)
MOSI_3V3: J3.3, J4.2 (CMD), U1.3 (A2), U3.5 (DI/IO_{0})
unnamed: D1.1 (K), R1.2
unnamed: J1.2, R2.2
unnamed: C4.2, U2.21 (AREF)
PHI2: J2.PHI2, U2.24 (PC1)
RESB: J2.RESB, U2.1 (~RESET/PC6)
RWB: J2.RWB, U2.26 (PC3)
SCK: D1.2 (A), J1.1, U1.20 (B1), U2.19 (PB5)
SCK_3V3: J3.2, J4.5 (CLK), U1.1 (A1), U3.6 (CLK)
VCC: C1.2, C2.2, C8.1, C9.1, J2.VCC, U1.19 (VCCB), U2.7 (VCC), U2.20 (AVCC), U4.16 (VCC), U5.1 (VIN), U5.3 (ON/~OFF)
WP: U1.12 (B8), U2.28 (PC5)
WP_3V3: J4.WP, R3.2, U1.9 (A8)
XTAL1: C5.1, U2.9 (XTAL1/PB6), Y1.2
XTAL2: C6.1, U2.10 (XTAL2/PB7), Y1.1

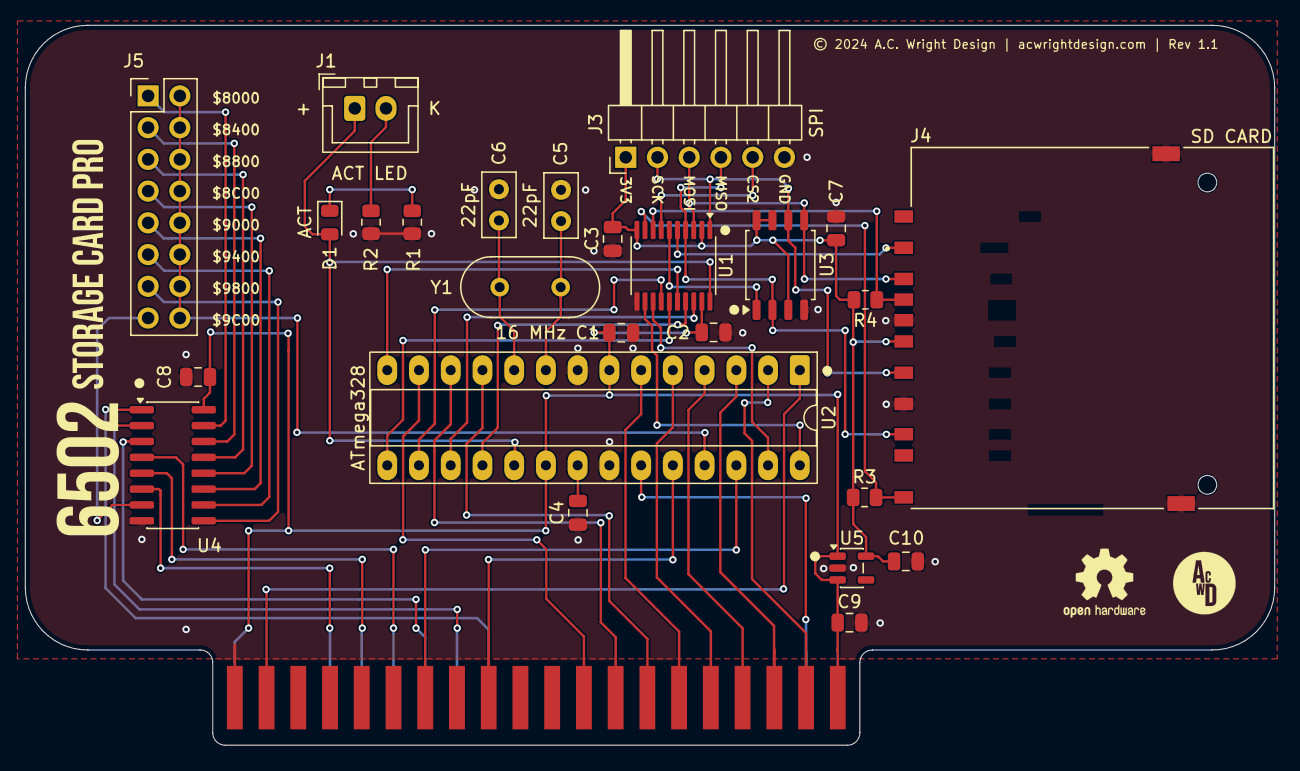
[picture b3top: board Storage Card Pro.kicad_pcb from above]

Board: 2 copper layers, 100.0 x 57.6 mm, 26 parts (0 on the bottom side), 51 nets.

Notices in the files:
README.md:
License:
Hardware designs are released under the [CERN Open Hardware Licence Version 2 – Permissive](https://ohwr.org/cern_ohl_p_v2.txt).
Firmware is released under the MIT License — [KEH Controller](./Firmware/KEH%20Controller/LICENSE), [PS2 Keyboard Controller](./Firmware/PS2%20Keyboard%20Controller/LICENSE), [STP Controller](./Firmware/STP%20Controller/LICENSE).
Hardware/Backplane Pro/Rev 1.1/Backplane Pro.kicad_pcb:
© 2026 A.C. Wright Design | acwrightdesign.com | Rev 1.1
Hardware/Backplane/Rev 1.1/Backplane.kicad_pcb:
© 2024 A.C. Wright Design | acwrightdesign.com | Rev 1.1
